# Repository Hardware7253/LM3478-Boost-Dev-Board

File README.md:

# LM3478 Boost Dev Board
A dev board for an LM3478 controlled boost converter

Contains two python calculators for selecting appropriate main components and compensation components

## PCB

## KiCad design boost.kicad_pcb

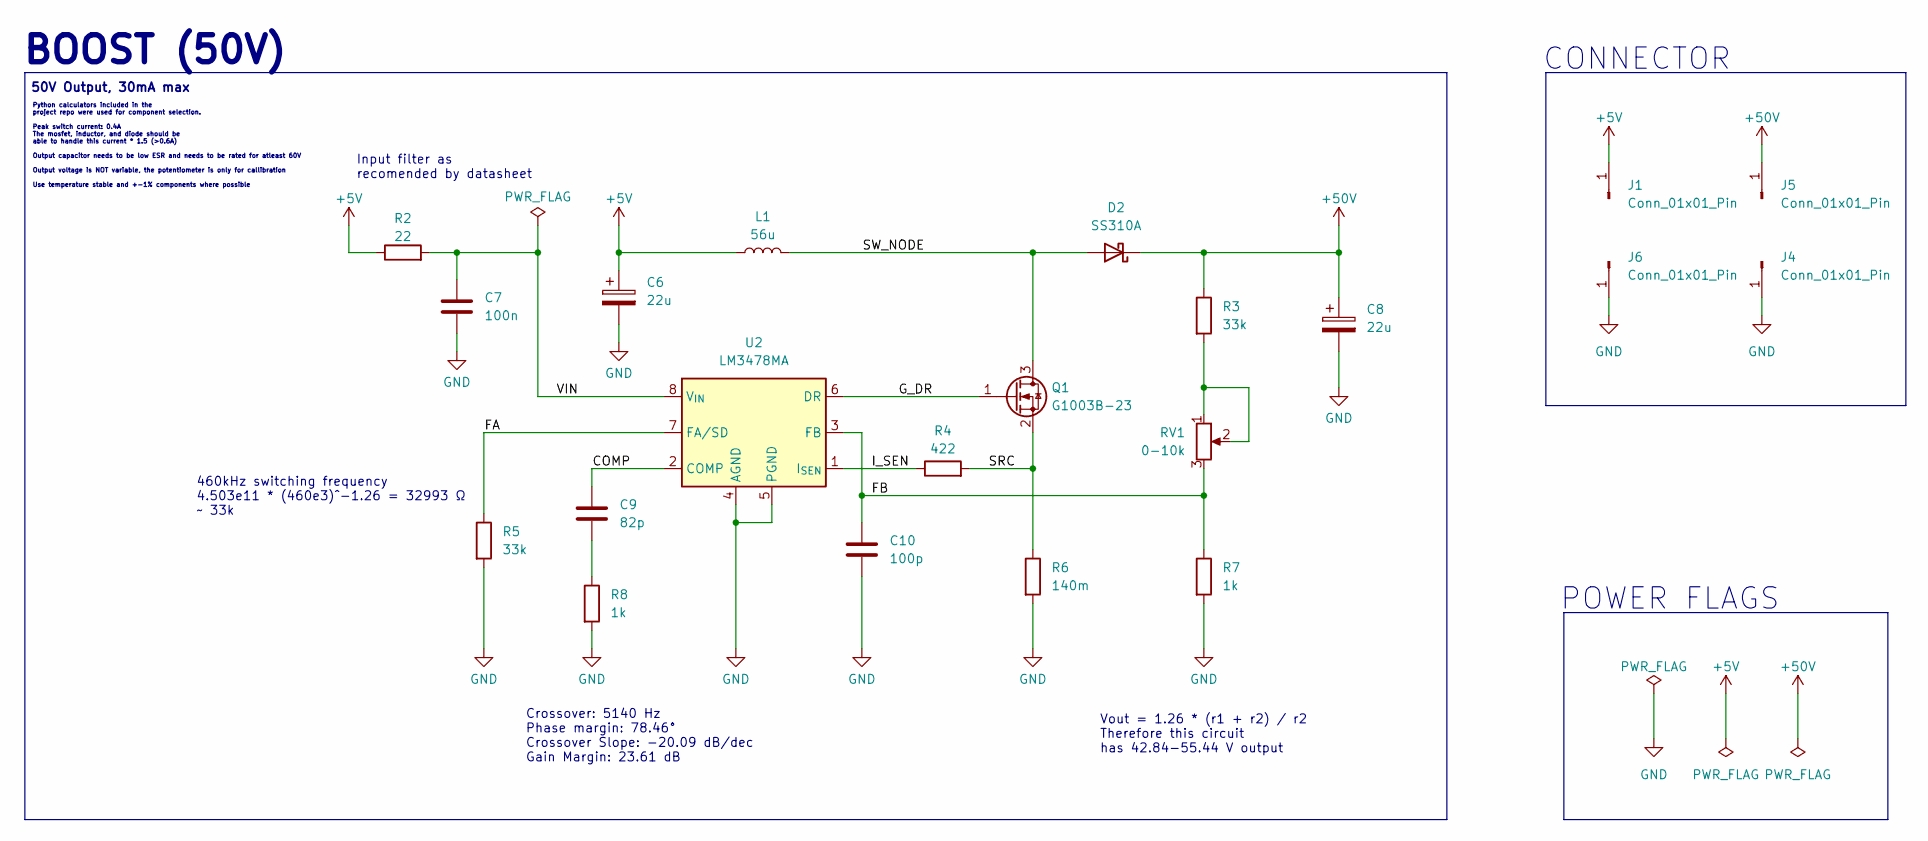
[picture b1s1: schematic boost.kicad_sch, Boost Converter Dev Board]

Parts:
C6, C8: 22u; CP_Radial_D6.3mm_P2.50mm; LCSC PART # C44606504
C7: 100n; C_0603_1608Metric; LCSC PART # C15725
C9: 82p; C_0603_1608Metric; LCSC PART # C1864236
C10: 100p; C_0603_1608Metric; LCSC PART # C7503509
D2: SS310A; D_SMA; LCSC PART # C48996628
J1, J4, J5, J6: Conn_01x01_Pin; PinHeader_1x01_P2.54mm_Vertical
L1: 56u; Chilisin SCDS105R; LCSC PART # C329728
Q1: G1003B-23; SOT-23-3; LCSC PART # C22362809
R2: 22; R_0603_1608Metric; LCSC PART # C48996824
R3, R5: 33k; R_0603_1608Metric; LCSC PART # C2907028
R4: 422; R_0603_1608Metric; LCSC PART # C5204003
R6: 140m; R_1206_3216Metric; LCSC PART # C37935
R7, R8: 1k; R_0603_1608Metric; LCSC PART # C2907002
RV1: 0-10k; Potentiometer_Bourns_TC33X_Vertical; LCSC PART # C719176
U2: LM3478MA; SOIC-8_3.9x4.9mm_P1.27mm; LCSC PART # C115907

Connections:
+5V: C6.1, J1.1, L1.1, R2.1
+50V: C8.1, D2.1 (K), J5.1, R3.1
/COMP: C9.1, U2.2 (COMP)
/FA: R5.1, U2.7 (FA/SD)
/FB: C10.1, R7.1, RV1.3, U2.3 (FB)
/G_DR: Q1.1 (G), U2.6 (DR)
/I_SEN: R4.1, U2.1 (I_{SEN})
/SRC: Q1.2 (S), R4.2, R6.1
/SW_NODE: D2.2 (A), L1.2, Q1.3 (D)
/VIN: C7.1, R2.2, U2.8 (V_{IN})
GND: C6.2, C7.2, C8.2, C10.2, J4.1, J6.1, R5.2, R6.2, R7.2, R8.2, U2.4 (AGND), U2.5 (PGND)
unnamed: C9.2, R8.1
unnamed: R3.2, RV1.1, RV1.2

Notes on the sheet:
Python calculators included in the project repo were used for component selection. Peak switch current: 0.4A The mosfet, inductor, and diode should be able to handle this current * 1.5 (>0.6A) Output capacitor needs to be low ESR and needs to be rated for atleast 60V Output voltage is NOT variable,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
460kHz switching frequency 4.503e11 * (460e3)^-1.26 = 32993 Ω ~ 33k
BOOST (50V)
Vout = 1.26 * (r1 + r2) / r2 Therefore this circuit has 42.84-55.44 V output
CONNECTOR
Crossover: 5140 Hz Phase margin: 78.46° Crossover Slope: -20.09 dB/dec Gain Margin: 23.61 dB
Input filter as recomended by datasheet
POWER FLAGS
50V Output, 30mA max

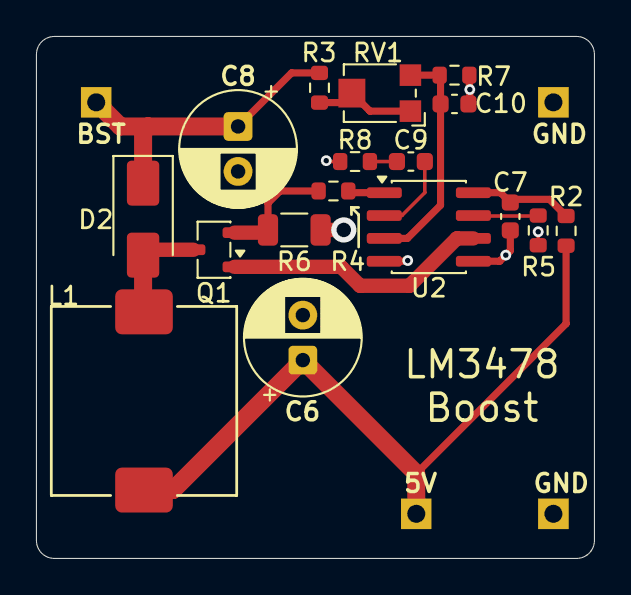
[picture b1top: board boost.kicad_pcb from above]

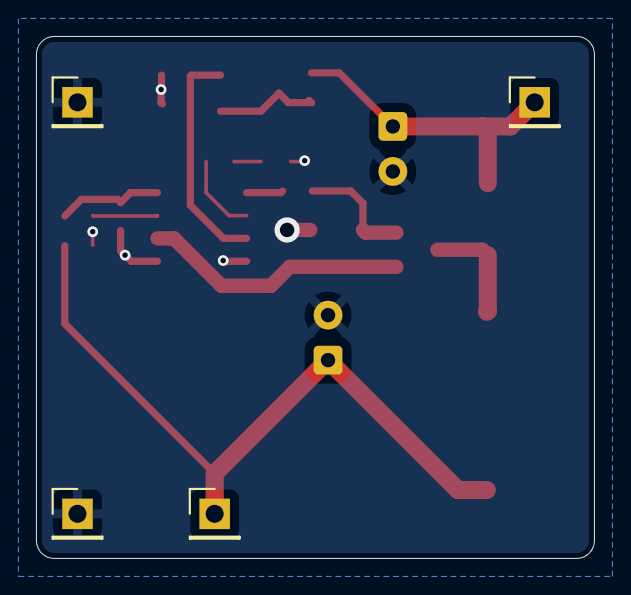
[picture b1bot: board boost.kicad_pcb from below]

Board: 2 copper layers, 31.0 x 29.0 mm, 21 parts (4 on the bottom side), 13 nets.

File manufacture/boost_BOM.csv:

"Reference","Value","Footprint","Qty","LCSC PART #"
"C6,C8","22u","Capacitor_SMD:CP_Elec_6.3x9.9","2","C19270543"
"C7","100n","Capacitor_SMD:C_0603_1608Metric","1","C15725"
"C9,C10","120p","Capacitor_SMD:C_0603_1608Metric","2","C18438"
"D2","SS310A","Diode_SMD:D_SMA","1","C48996628"
"J1,J4,J5,J6","Conn_01x01_Pin","Connector_PinHeader_2.54mm:PinHeader_1x01_P2.54mm_Vertical","4",""
"L1","56u","CustomFootprints:Chilisin SCDS105R","1","C329728"
"Q1","G1003B-23","Package_TO_SOT_SMD:SOT-23-3","1","C22362809"
"R2","22","Resistor_SMD:R_0603_1608Metric","1","C48996824"
"R3,R5","33k","Resistor_SMD:R_0603_1608Metric","2","C2907028"
"R4","390","Resistor_SMD:R_0603_1608Metric","1","C49653317"
"R6","150m","Resistor_SMD:R_1206_3216Metric","1","C37936"
"R7,R8","1k","Resistor_SMD:R_0603_1608Metric","2","C2907002"
"RV1","0-10k","CustomFootprints:Potentiometer_Bourns_TC33X_Vertical","1","C719176"
"U2","LM3478MA","Package_SO:SOIC-8_3.9x4.9mm_P1.27mm","1","C115907"

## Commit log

2025-11-23 Initial commit
    In the same formfactor as the power supply from OperationUrd.
    The formfactor will change in subsequent commits
2025-11-27 Switched to breadboard formfactor
    Also added files for GH
2025-11-27 Added calculators
    Changed component values to match calculator recommended values
2025-11-28 Changed to THT cap
    Low ESR THT caps are easier to find. But I'm really changing cause the
    SMD cap I wanted went out of stock :(
2025-12-19 Added efficiency tests to reference design
